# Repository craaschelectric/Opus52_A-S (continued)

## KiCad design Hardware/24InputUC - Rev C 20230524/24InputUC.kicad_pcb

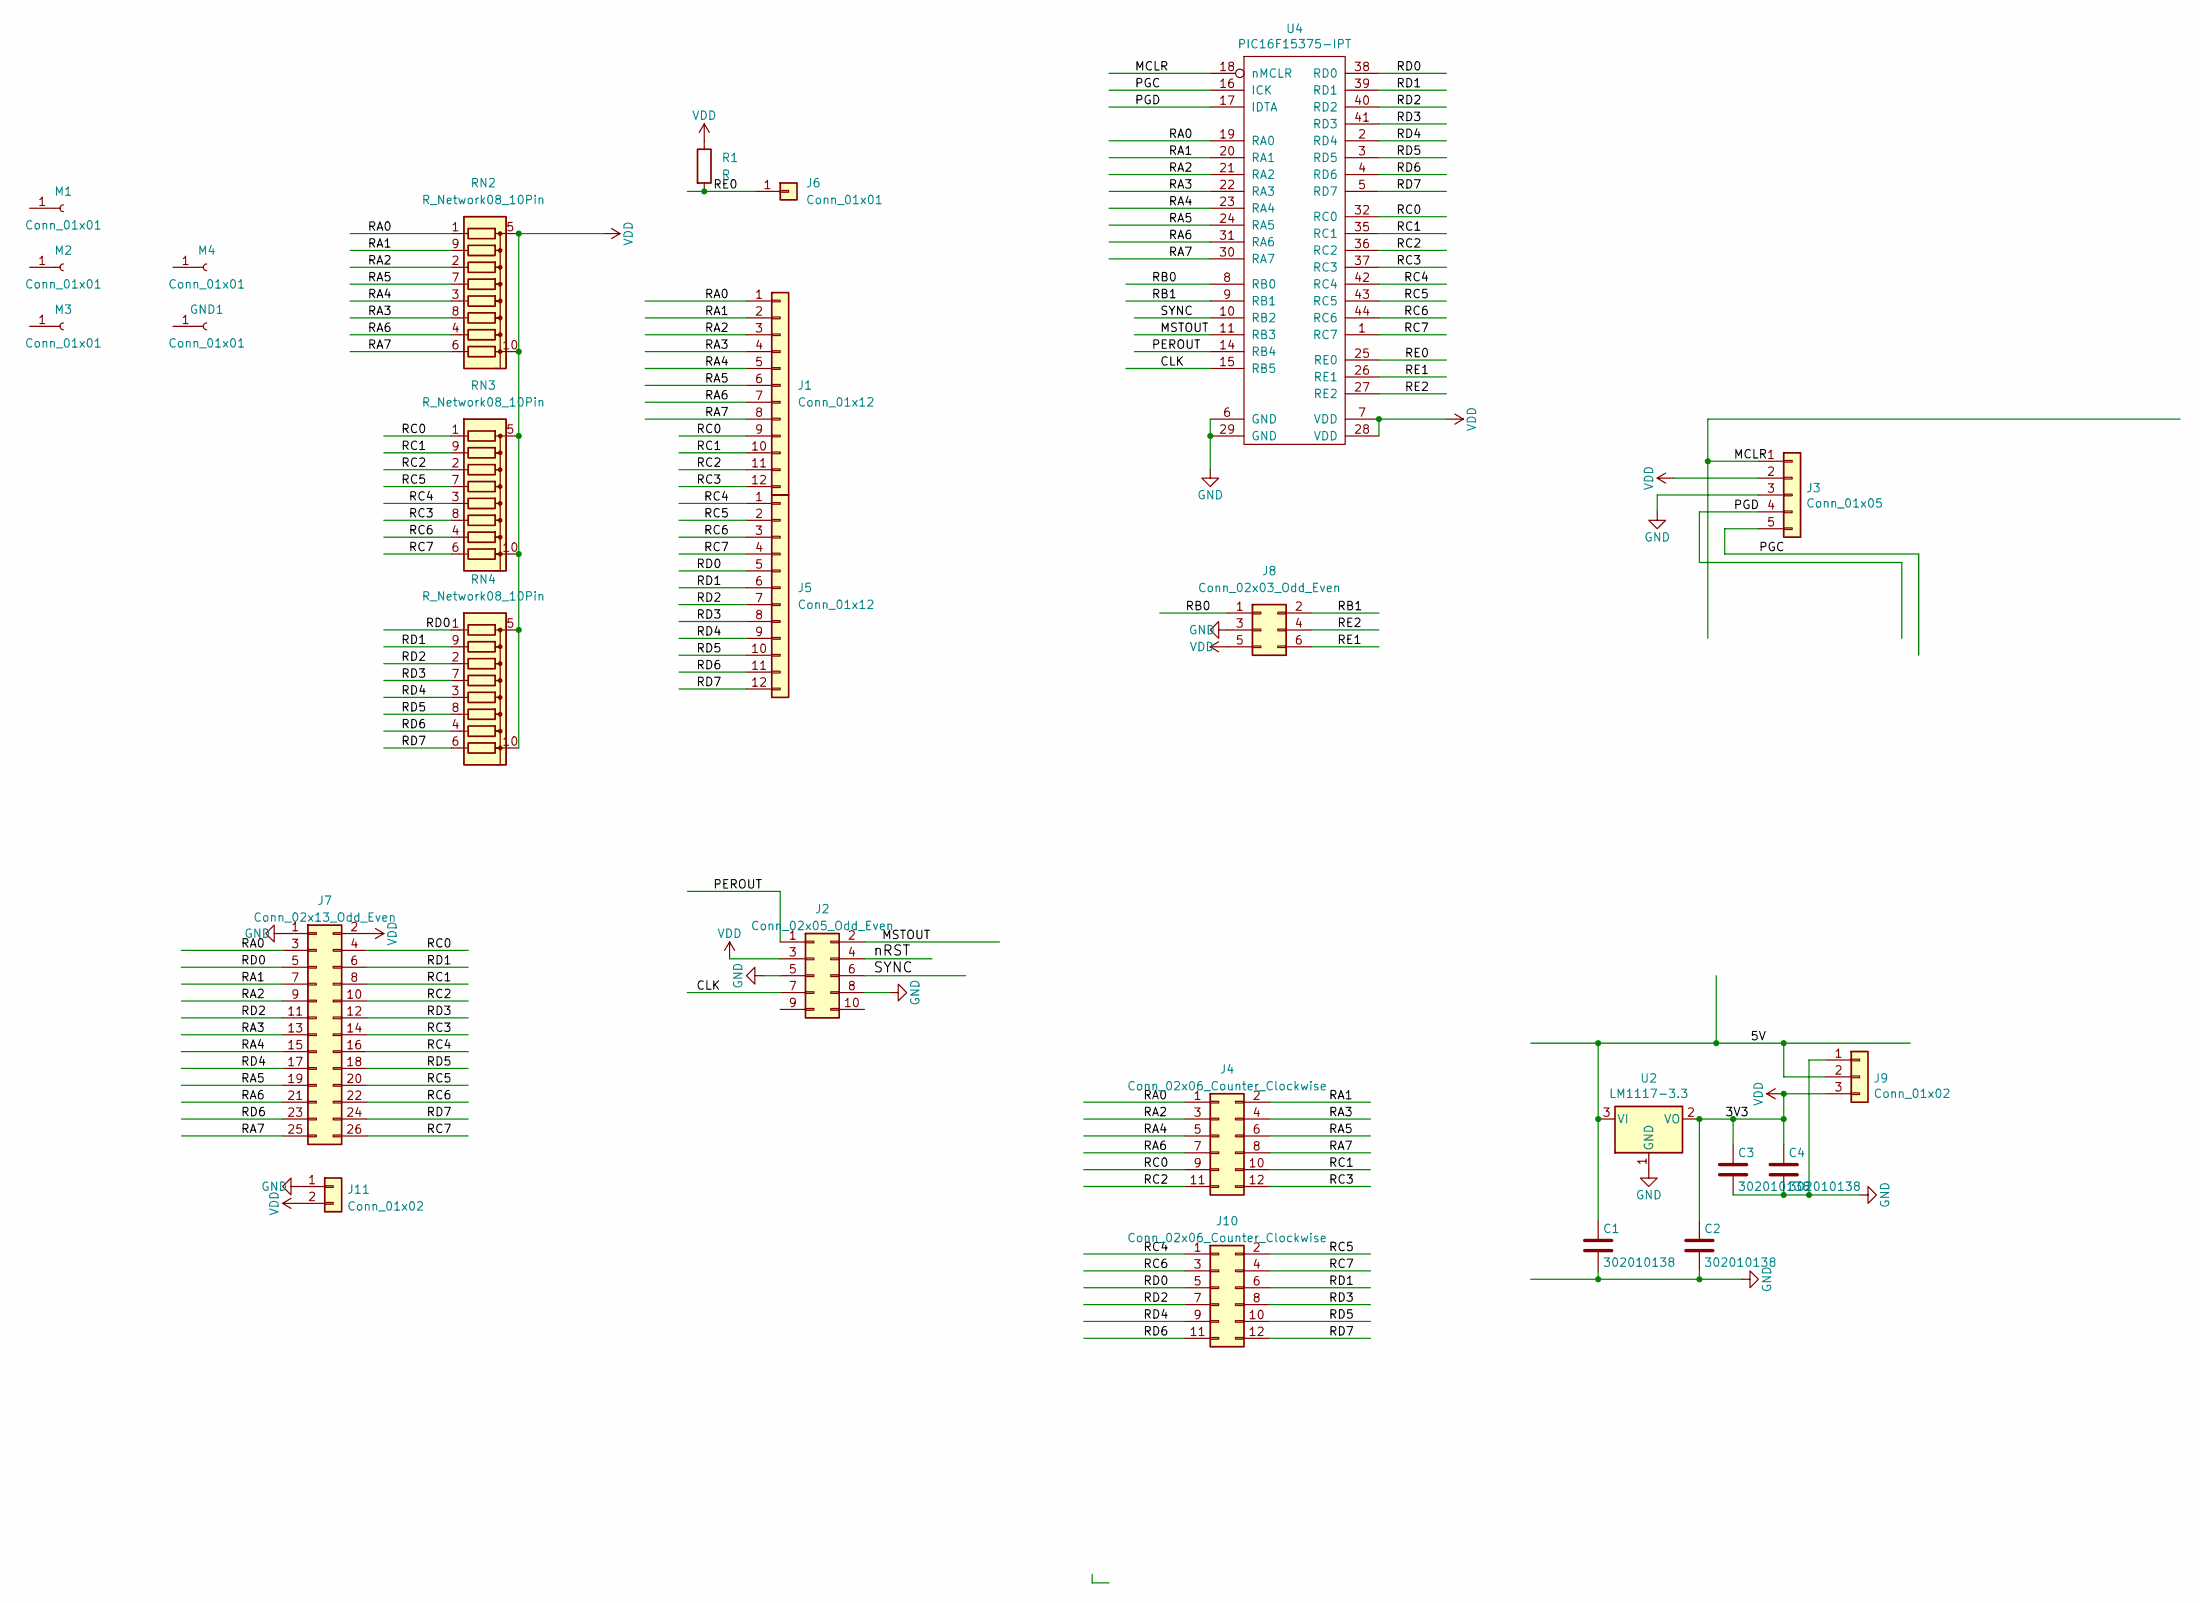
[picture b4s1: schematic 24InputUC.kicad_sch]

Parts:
C1, C3: 302010138; C_0805_2012Metric_Pad1.18x1.45mm_HandSolder
C2, C4: 302010138; C_0603_1608Metric_Pad1.08x0.95mm_HandSolder
GND1: Conn_01x01; KK156-1
J1, J5: Conn_01x12; KK156-12
J2: Conn_02x05_Odd_Even; RibbonCableSocket_10_OddEven
J3: Conn_01x05; PinHeader_1x06_P2.54mm_Vertical
J4, J10: Conn_02x06_Counter_Clockwise; RibbonCableSocket_12_OddEven
J6: Conn_01x01; KK156-1
J7: Conn_02x13_Odd_Even; RibbonCableSocket_26_OddEven
J8: Conn_02x03_Odd_Even; RibbonCableSocket_6_OddEven
J9: Conn_01x02; PinHeader_1x03_P2.54mm_Vertical
J11: Conn_01x02; PinHeader_1x02_P2.54mm_Vertical
M1, M2, M3, M4: Conn_01x01; Mounting#4
R1: R; R_0603_1608Metric_Pad0.98x0.95mm_HandSolder
RN2, RN3, RN4: R_Network08_10Pin; EXBA10P
U2: LM1117-3.3; SOT-223-3_TabPin2
U4: PIC16F15375-IPT; TQFP-44_10x10mm_P0.8mm

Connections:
/5V: C1.1, J9.2, U2.3 (VI)
/CLK: J2.7, U4.15 (RB5)
/MCLR: J3.1, U4.18 (nMCLR)
/MSTOUT: J2.2, U4.11 (RB3)
/PEROUT: J2.1, U4.14 (RB4)
/PGC: J3.5, U4.16 (ICK)
/PGD: J3.4, U4.17 (IDTA)
/RA0: J1.1, J4.1, J7.3, RN2.1 (common), U4.19 (RA0)
/RA1: J1.2, J4.2, J7.7, RN2.9 (R8), U4.20 (RA1)
/RA2: J1.3, J4.3, J7.9, RN2.2 (R1), U4.21 (RA2)
/RA3: J1.4, J4.4, J7.13, RN2.8 (R7), U4.22 (RA3)
/RA4: J1.5, J4.5, J7.15, RN2.3 (R2), U4.23 (RA4)
/RA5: J1.6, J4.6, J7.19, RN2.7 (R6), U4.24 (RA5)
/RA6: J1.7, J4.7, J7.21, RN2.4 (R3), U4.31 (RA6)
/RA7: J1.8, J4.8, J7.25, RN2.6 (R5), U4.30 (RA7)
/RB0: J8.1, U4.8 (RB0)
/RB1: J8.2, U4.9 (RB1)
/RC0: J1.9, J4.9, J7.4, RN3.1 (common), U4.32 (RC0)
/RC1: J1.10, J4.10, J7.8, RN3.9 (R8), U4.35 (RC1)
/RC2: J1.11, J4.11, J7.10, RN3.2 (R1), U4.36 (RC2)
/RC3: J1.12, J4.12, J7.14, RN3.8 (R7), U4.37 (RC3)
/RC4: J5.1, J7.16, J10.1, RN3.3 (R2), U4.42 (RC4)
/RC5: J5.2, J7.20, J10.2, RN3.7 (R6), U4.43 (RC5)
/RC6: J5.3, J7.22, J10.3, RN3.4 (R3), U4.44 (RC6)
/RC7: J5.4, J7.26, J10.4, RN3.6 (R5), U4.1 (RC7)
/RD0: J5.5, J7.5, J10.5, RN4.1 (common), U4.38 (RD0)
/RD1: J5.6, J7.6, J10.6, RN4.9 (R8), U4.39 (RD1)
/RD2: J5.7, J7.11, J10.7, RN4.2 (R1), U4.40 (RD2)
/RD3: J5.8, J7.12, J10.8, RN4.7 (R6), U4.41 (RD3)
/RD4: J5.9, J7.17, J10.9, RN4.3 (R2), U4.2 (RD4)
/RD5: J5.10, J7.18, J10.10, RN4.8 (R7), U4.3 (RD5)
/RD6: J5.11, J7.23, J10.11, RN4.4 (R3), U4.4 (RD6)
/RD7: J5.12, J7.24, J10.12, RN4.6 (R5), U4.5 (RD7)
/RE0: J6.1, R1.2, U4.25 (RE0)
/RE1: J8.6, U4.26 (RE1)
/RE2: J8.4, U4.27 (RE2)
/SYNC: J2.6, U4.10 (RB2)
/nRST: J2.4
GND: C1.2, C2.2, C3.2, C4.2, J2.5, J2.8, J3.3, J7.1, J8.3, J9.1, J11.1, U2.1 (GND), U4.6 (GND), U4.29 (GND)
VDD: C2.1, C3.1, C4.1, J2.3, J3.2, J7.2, J8.5, J9.3, J11.2, R1.1, RN2.5 (R4), RN2.10 (R9), RN3.5 (R4), RN3.10 (R9), RN4.5 (R4), RN4.10 (R9), U2.2 (VO), U4.7 (VDD), U4.28 (VDD)

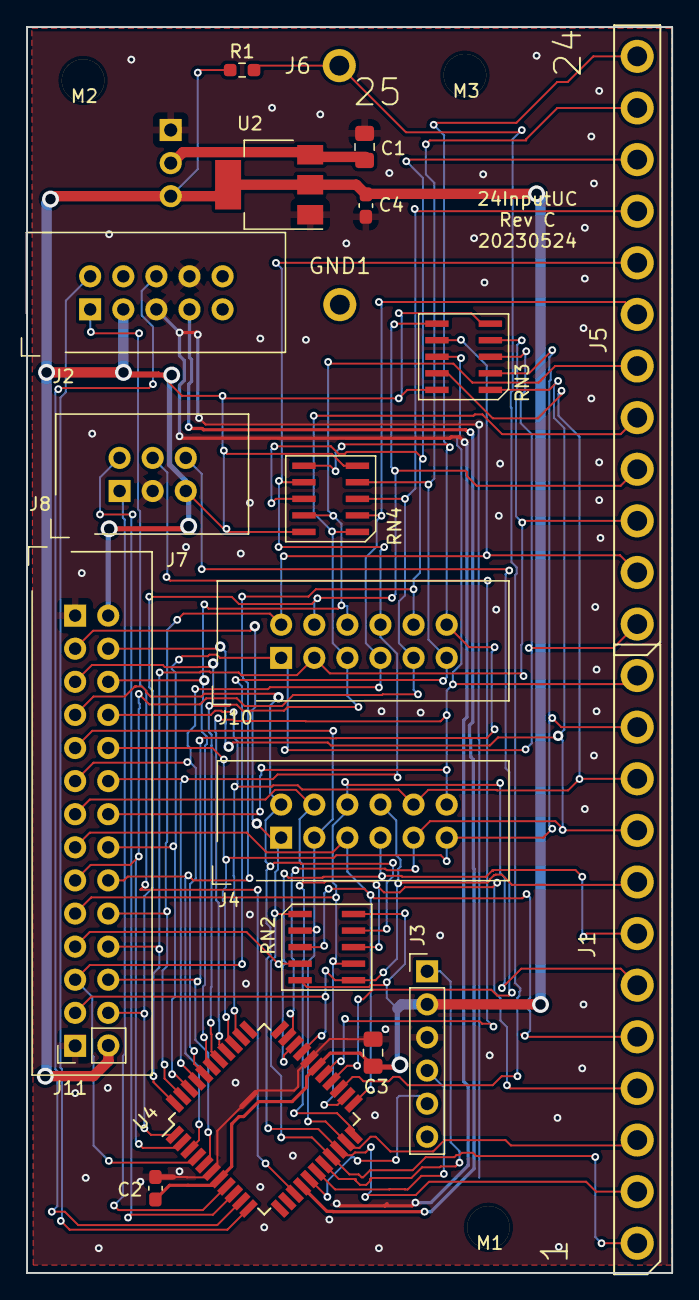
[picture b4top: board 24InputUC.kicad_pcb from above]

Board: 2 copper layers, 49.5 x 95.6 mm, 25 parts (1 on the bottom side), 39 nets.

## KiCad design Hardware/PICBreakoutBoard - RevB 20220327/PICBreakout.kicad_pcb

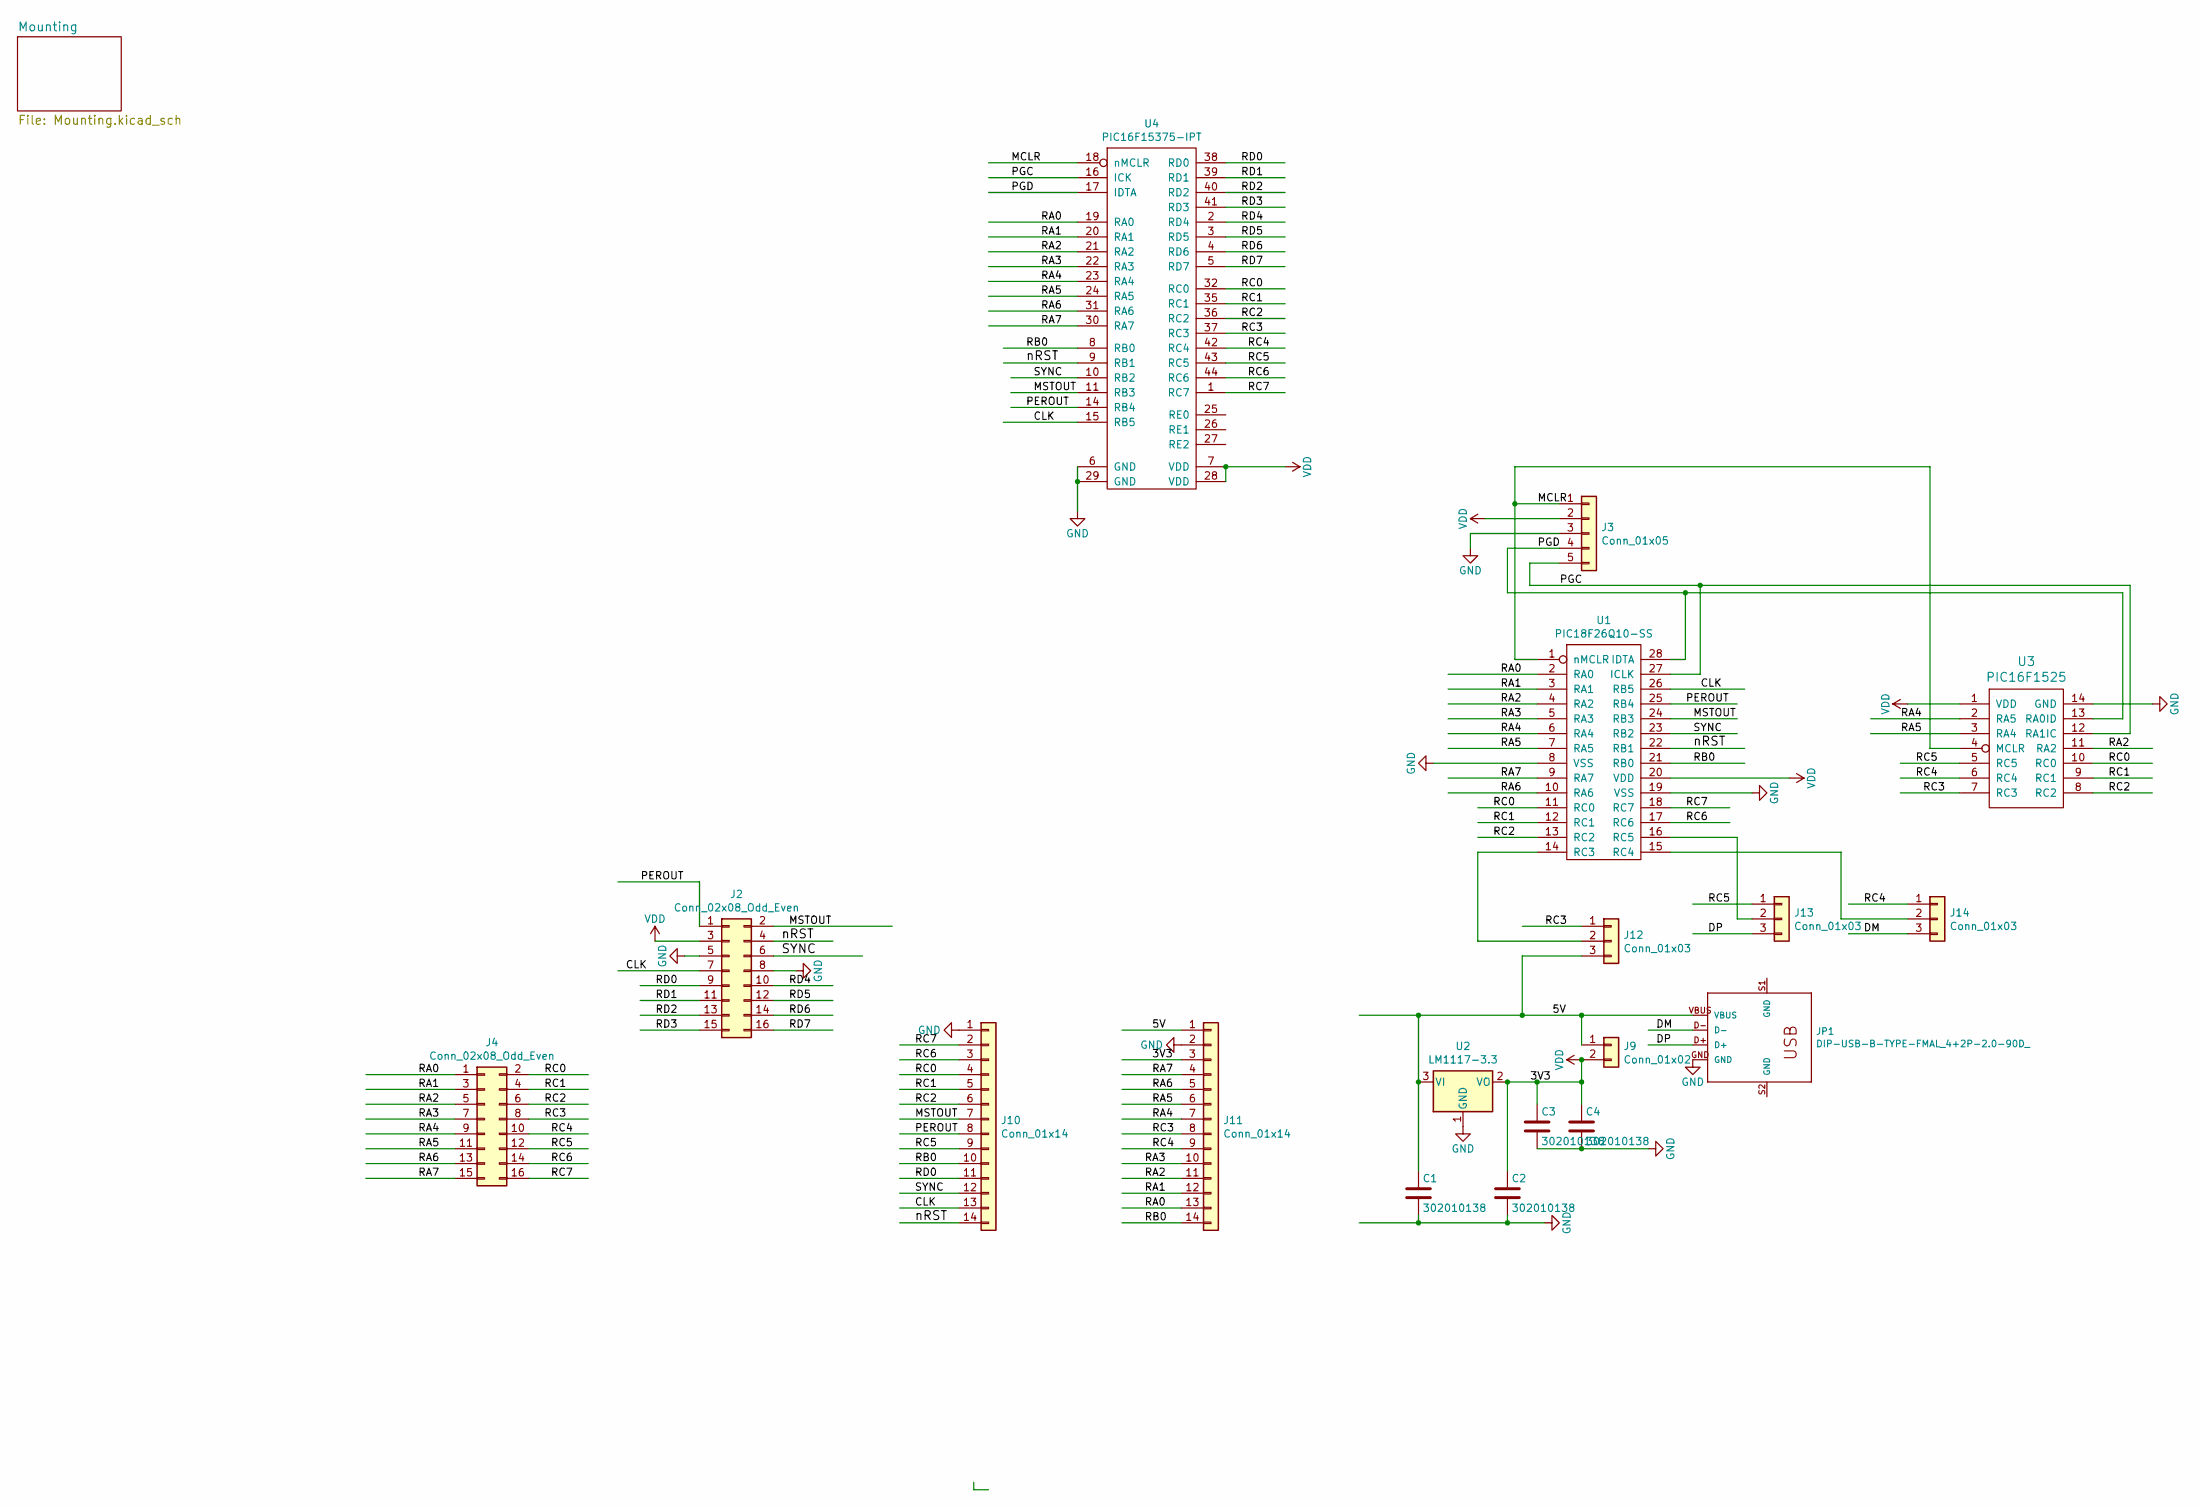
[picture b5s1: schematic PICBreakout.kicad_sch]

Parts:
C1, C3: 302010138; C_0805_2012Metric_Pad1.18x1.45mm_HandSolder
C2, C4: 302010138; C_0603_1608Metric_Pad1.08x0.95mm_HandSolder
J2, J4: Conn_02x08_Odd_Even; RibbonCableSocket_16_OddEven
J3: Conn_01x05; PinHeader_1x06_P2.54mm_Vertical
J9: Conn_01x02; H2-2.54
J10, J11: Conn_01x14; PinSocket_1x14_P2.54mm_Vertical
J12, J13, J14: Conn_01x03; 0603Jumper
JP1: DIP-USB-B-TYPE-FMAL_4+2P-2.0-90D_; USB4+2-2.5-90D-15.8X12MM
U1: PIC18F26Q10-SS; SSOP-28_5.3x10.2mm_P0.65mm
U2: LM1117-3.3; SOT-223-3_TabPin2
U3: PIC16F1525; SO-14_3.9x8.65mm_P1.27mm
U4: PIC16F15375-IPT; TQFP-44_10x10mm_P0.8mm

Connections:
/5V: C1.1, J9.1, J11.1, J12.3, JP1.VBUS, U2.3 (VI)
/CLK: J2.7, J10.13, U1.26 (RB5), U4.15 (RB5)
/DM: J14.3, JP1.D-
/DP: J13.3, JP1.D+
/MCLR: J3.1, U1.1 (nMCLR), U3.4 (MCLR), U4.18 (nMCLR)
/MSTOUT: J2.2, J10.7, U1.24 (RB3), U4.11 (RB3)
/PEROUT: J2.1, J10.8, U1.25 (RB4), U4.14 (RB4)
/PGC: J3.5, U1.27 (ICLK), U3.12 (RA1IC), U4.16 (ICK)
/PGD: J3.4, U1.28 (IDTA), U3.13 (RA0ID), U4.17 (IDTA)
/RA0: J4.1, J11.13, U1.2 (RA0), U4.19 (RA0)
/RA1: J4.3, J11.12, U1.3 (RA1), U4.20 (RA1)
/RA2: J4.5, J11.11, U1.4 (RA2), U3.11 (RA2), U4.21 (RA2)
/RA3: J4.7, J11.10, U1.5 (RA3), U4.22 (RA3)
/RA4: J4.9, J11.7, U1.6 (RA4), U3.2 (RA5), U4.23 (RA4)
/RA5: J4.11, J11.6, U1.7 (RA5), U3.3 (RA4), U4.24 (RA5)
/RA6: J4.13, J11.5, U1.10 (RA6), U4.31 (RA6)
/RA7: J4.15, J11.4, U1.9 (RA7), U4.30 (RA7)
/RB0: J10.10, J11.14, U1.21 (RB0), U4.8 (RB0)
/RC0: J4.2, J10.4, U1.11 (RC0), U3.10 (RC0), U4.32 (RC0)
/RC1: J4.4, J10.5, U1.12 (RC1), U3.9 (RC1), U4.35 (RC1)
/RC2: J4.6, J10.6, U1.13 (RC2), U3.8 (RC2), U4.36 (RC2)
/RC3: J4.8, J11.8, J12.1, U3.7 (RC3), U4.37 (RC3)
/RC4: J4.10, J11.9, J14.1, U3.6 (RC4), U4.42 (RC4)
/RC5: J4.12, J10.9, J13.1, U3.5 (RC5), U4.43 (RC5)
/RC6: J4.14, J10.3, U1.17 (RC6), U4.44 (RC6)
/RC7: J4.16, J10.2, U1.18 (RC7), U4.1 (RC7)
/RD0: J2.9, J10.11, U4.38 (RD0)
/RD1: J2.11, U4.39 (RD1)
/RD2: J2.13, U4.40 (RD2)
/RD3: J2.15, U4.41 (RD3)
/RD4: J2.10, U4.2 (RD4)
/RD5: J2.12, U4.3 (RD5)
/RD6: J2.14, U4.4 (RD6)
/RD7: J2.16, U4.5 (RD7)
/SYNC: J2.6, J10.12, U1.23 (RB2), U4.10 (RB2)
/nRST: J2.4, J10.14, U1.22 (RB1), U4.9 (RB1)
GND: C1.2, C2.2, C3.2, C4.2, J2.5, J2.8, J3.3, J10.1, J11.2, JP1.GND, U1.8 (VSS), U1.19 (VSS), U2.1 (GND), U3.14 (GND), U4.6 (GND), U4.29 (GND)
unnamed: J12.2, U1.14 (RC3)
unnamed: J13.2, U1.16 (RC5)
unnamed: J14.2, U1.15 (RC4)
VDD: C2.1, C3.1, C4.1, J2.3, J3.2, J9.2, J11.3, U1.20 (VDD), U2.2 (VO), U3.1 (VDD), U4.7 (VDD), U4.28 (VDD)

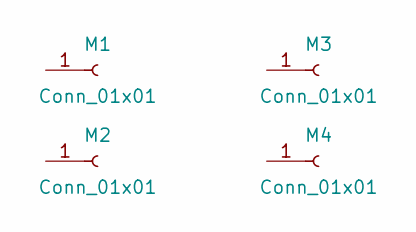
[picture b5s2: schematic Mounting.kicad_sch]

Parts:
M1, M2, M3, M4: Conn_01x01; Mounting#4

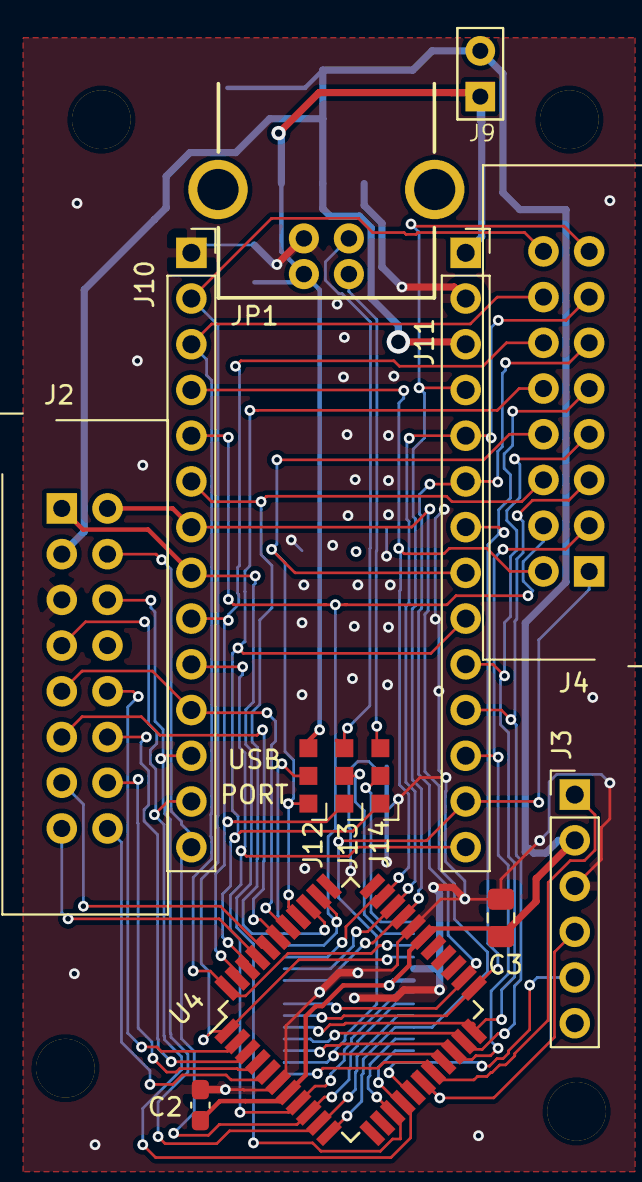
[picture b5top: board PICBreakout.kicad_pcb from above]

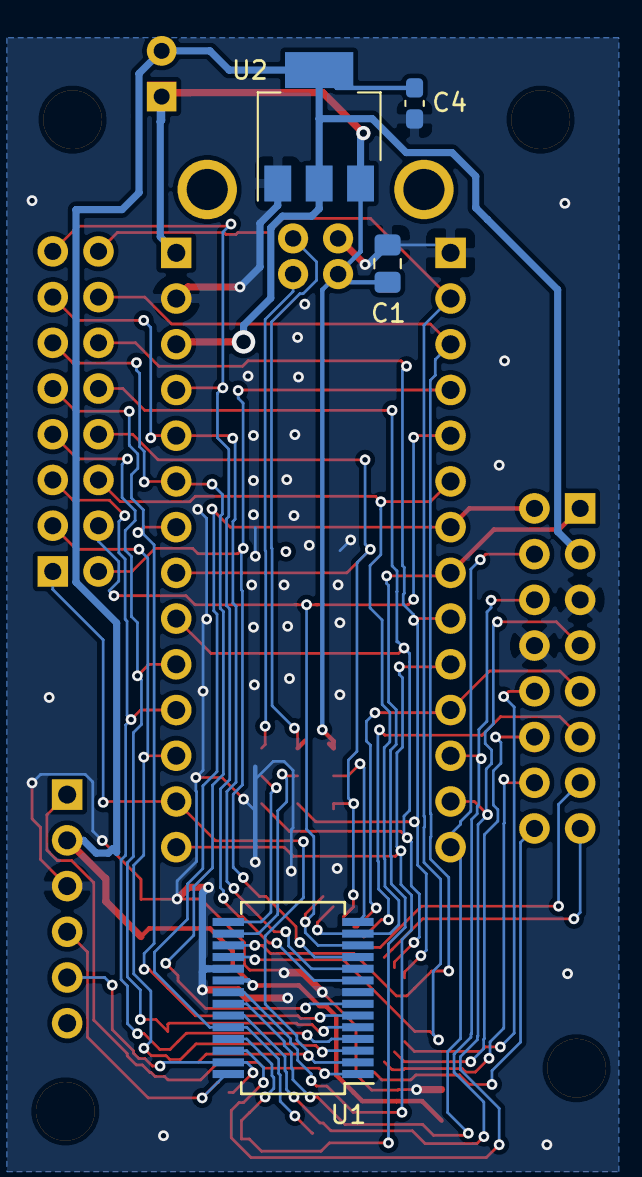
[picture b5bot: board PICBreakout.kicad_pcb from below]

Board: 2 copper layers, 21 parts (4 on the bottom side), 41 nets.

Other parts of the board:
Me: Conn_01x01; Mounting#4

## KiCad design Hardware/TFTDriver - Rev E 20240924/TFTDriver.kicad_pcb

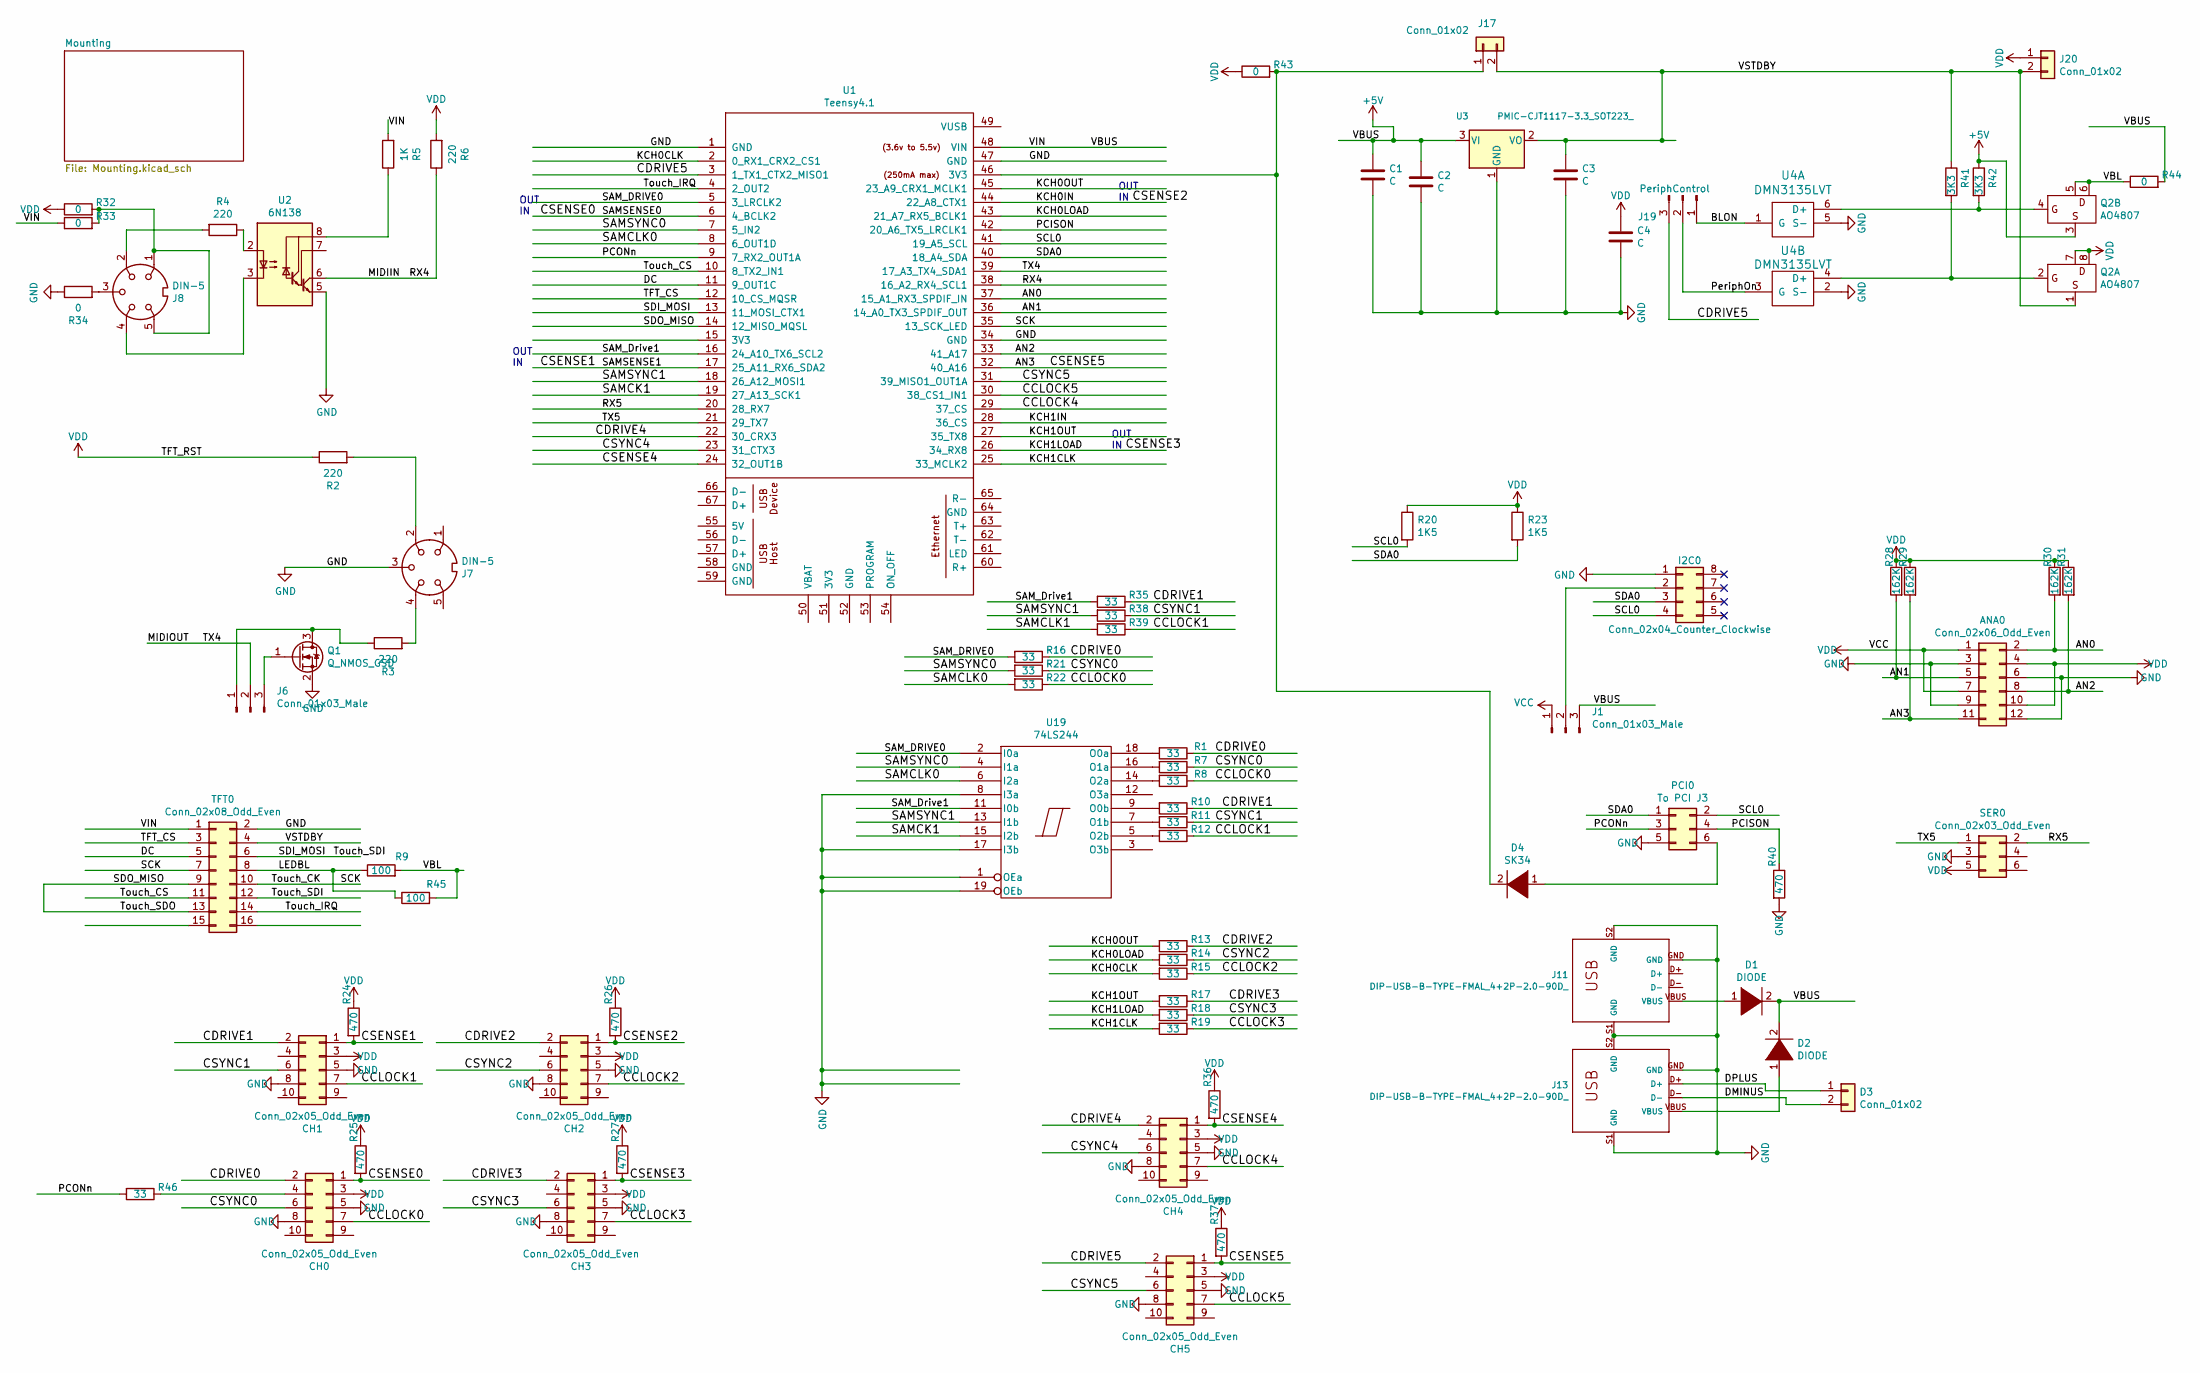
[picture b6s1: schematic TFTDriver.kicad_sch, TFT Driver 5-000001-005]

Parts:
ANA0: Conn_02x06_Odd_Even; RibbonCableSocket_12_OddEven
C1, C4: C; C_0603_1608Metric_Pad1.08x0.95mm_HandSolder
C2, C3: C; C_0805_2012Metric_Pad1.18x1.45mm_HandSolder
CH0, CH1, CH2, CH3, CH4, CH5: Conn_02x05_Odd_Even; RibbonCableSocket_10_OddEven
D1, D2: DIODE; D_SMA_Handsoldering_APin1
D3: Conn_01x02; PinHeader_1x02_P2.54mm_Vertical
D4: SK34; D_SMA_Handsoldering
I2C0: Conn_02x04_Counter_Clockwise; RibbonCableSocket_8_CCW
J1: Conn_01x03_Male; PinHeader_1x03_P2.54mm_Vertical
J6: Conn_01x03_Male; H3-2.54
J7, J8: DIN-5; DIN5_KCDX-5S-S2
J11, J13: DIP-USB-B-TYPE-FMAL_4+2P-2.0-90D_; USB4+2-2.5-90D-15.8X12MM
J17, J20: Conn_01x02; PinHeader_1x02_P2.54mm_Vertical
J19: PeriphControl; 0603Jumper
PCI0: To PCI J3; RibbonCableSocket_6_OddEven
Q1: Q_NMOS_GSD; SOT-23_Handsoldering
Q2: AO4807; SOIC-8_3.9x4.9mm_P1.27mm
R1, R7, R8, R10, R11, R12, R13, R14, R15, R16, R17, R18, R19, R21, R22, R35, R38, R39, R46: 33; R_0603_1608Metric_Pad0.98x0.95mm_HandSolder
R2, R3, R4, R6: 220; R_0603_1608Metric_Pad0.98x0.95mm_HandSolder
R5: 1K; R_0603_1608Metric_Pad0.98x0.95mm_HandSolder
R9: 100; PinHeader_1x02_P2.54mm_Vertical
R20, R23: 1K5; R_0603_1608Metric_Pad0.98x0.95mm_HandSolder
R24, R25, R26, R27, R36, R37, R40: 470; R_0603_1608Metric_Pad0.98x0.95mm_HandSolder
R28, R29, R30, R31: 162K; R_0603_1608Metric_Pad0.98x0.95mm_HandSolder
R32, R33, R34, R43, R44: 0; R_0603_1608Metric_Pad0.98x0.95mm_HandSolder
R41, R42: 3K3; R_0603_1608Metric_Pad0.98x0.95mm_HandSolder
R45: 100; R_1206_3216Metric_Pad1.30x1.75mm_HandSolder
SER0: Conn_02x03_Odd_Even; RibbonCableSocket_6_OddEven
TFT0: Conn_02x08_Odd_Even; RibbonCableSocket_16_OddEven
U1: Teensy4.1; Teensy41
U2: 6N138; DIP-8_W7.62mm
U3: PMIC-CJT1117-3.3_SOT223_; SOT-223; MPN CJT1117-3.3
U4: DMN3135LVT; SOT-23-6_Handsoldering
U19: 74LS244; SSOP-20_4.4x6.5mm_P0.65mm

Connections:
+5V: C1.1, C2.1, D1.2 (A), D2.2 (A), J1.3, Q2.3, R5.2, R33.1, R42.1, R44.2, TFT0.1, U1.48 (VIN), U3.3 (VI)
/AN0: ANA0.2, R30.2, U1.37 (15_A1_RX3_SPDIF_IN)
/AN1: ANA0.5, R28.2, U1.36 (14_A0_TX3_SPDIF_OUT)
/AN2: ANA0.8, R31.2, U1.33 (41_A17)
/AN3: ANA0.11, CH5.1, R29.2, R37.2, U1.32 (40_A16)
/BLON: J19.1, U4.1 (G)
/CCLOCK0: CH0.7, R8.1, R22.1
/CCLOCK1: CH1.7, R12.1, R39.1
/CCLOCK2: CH2.7, R15.1
/CCLOCK3: CH3.7, R19.1
/CCLOCK4: CH4.7, U1.29 (37_CS)
/CCLOCK5: CH5.7, U1.30 (38_CS1_IN1)
/CDRIVE0: CH0.2, R1.1, R16.1
/CDRIVE1: CH1.2, R10.1, R35.1
/CDRIVE2: CH2.2, R13.1
/CDRIVE3: CH3.2, R17.1
/CDRIVE4: CH4.2, U1.22 (30_CRX3)
/CDRIVE5: CH5.2, J19.3, U1.3 (1_TX1_CTX2_MISO1)
/CSENSE0: CH0.1, R25.2, U1.6 (4_BCLK2)
/CSENSE1: CH1.1, R24.2, U1.17 (25_A11_RX6_SDA2)
/CSENSE2: CH2.1, R26.2, U1.44 (22_A8_CTX1)
/CSENSE3: CH3.1, R18.2, R27.2, U1.26 (34_RX8)
/CSENSE4: CH4.1, R36.2, U1.24 (32_OUT1B)
/CSYNC0: CH0.6, R7.1, R21.1
/CSYNC1: CH1.6, R11.1, R38.1
/CSYNC2: CH2.6, R14.1
/CSYNC3: CH3.6, R18.1
/CSYNC4: CH4.6, U1.23 (31_CTX3)
/CSYNC5: CH5.6, U1.31 (39_MISO1_OUT1A)
/DC: TFT0.5, U1.11 (9_OUT1C)
/DMINUS: D3.2, J13.D-
/DPLUS: D3.1, J13.D+
/KCH0CLK: R15.2, U1.2 (0_RX1_CRX2_CS1)
/KCH0LOAD: R14.2, U1.43 (21_A7_RX5_BCLK1)
/KCH0OUT: R13.2, U1.45 (23_A9_CRX1_MCLK1)
/KCH1CLK: R19.2, U1.25 (33_MCLK2)
/KCH1IN: U1.28 (36_CS)
/KCH1OUT: R17.2, U1.27 (35_TX8)
/LEDBL: R9.1, R45.1, TFT0.8
/MIDIIN: R6.1, U1.38 (16_A2_RX4_SCL1), U2.6 (VO2)
/MIDIOUT: J6.2, U1.39 (17_A3_TX4_SDA1)
/PCISON: PCI0.4, R40.1, U1.42 (20_A6_TX5_LRCLK1)
/PCONn: PCI0.3, R46.2, U1.9 (7_RX2_OUT1A)
/PeriphOn: J19.2, U4.3 (G)
/RX5: SER0.2, U1.20 (28_RX7)
/SAMCK1: U1.19 (27_A13_SCK1), U19.15 (I2b)
/SAMCLK0: R22.2, U1.8 (6_OUT1D), U19.6 (I2a)
/SAMCLK1: R39.2
/SAMSYNC0: R21.2, U1.7 (5_IN2), U19.4 (I1a)
/SAMSYNC1: R38.2, U1.18 (26_A12_MOSI1), U19.13 (I1b)
/SAM_DRIVE0: R16.2, U1.5 (3_LRCLK2), U19.2 (I0a)
/SAM_Drive1: R35.2, U1.16 (24_A10_TX6_SCL2), U19.11 (I0b)
/SCK: TFT0.7, TFT0.10, U1.35 (13_SCK_LED)
/SCL0: I2C0.4, PCI0.2, R20.2, U1.41 (19_A5_SCL)
/SDA0: I2C0.3, PCI0.1, R23.2, U1.40 (18_A4_SDA)
/SDI_MOSI: TFT0.6, TFT0.12, U1.13 (11_MOSI_CTX1)
/SDO_MISO: TFT0.9, TFT0.13, U1.14 (12_MISO_MQSL)
/TFT_CS: TFT0.3, U1.12 (10_CS_MQSR)
/TX5: SER0.1, U1.21 (29_TX7)
/Touch_CS: TFT0.11, U1.10 (8_TX2_IN1)
/Touch_IRQ: TFT0.14, U1.4 (2_OUT2)
/VBL: Q2.5, Q2.6, R9.2, R44.1, R45.2
/VSTDBY: C3.1, J17.2, J20.2, Q2.1, R41.1, TFT0.4, U3.2 (VO), U3.4
GND: ANA0.3, ANA0.6, ANA0.9, ANA0.12, C1.2, C2.2, C3.2, C4.2, CH0.5, CH0.8, CH1.5, CH1.8, CH2.5, CH2.8, CH3.5, CH3.8, CH4.5, CH4.8, CH5.5, CH5.8, I2C0.1, J7.3, J11.GND, J11.S1 (GND), J11.S2 (GND), J13.GND, J13.S1 (GND), J13.S2 (GND), PCI0.5, Q1.2 (S), R34.1, R40.2, SER0.3, TFT0.2, U1.1 (GND), U1.34 (GND), U1.47 (GND), U2.5 (GND), U3.1 (GND), U4.2 (S-), U4.5 (S-), U19.1 (OEa), U19.8 (I3a), U19.10 (GND), U19.17 (I3b), U19.19 (OEb)
unnamed: CH0.4, R46.1
unnamed: D1.1 (K), J11.VBUS
unnamed: D2.1 (K), J13.VBUS
unnamed: D4.2 (A), J17.1, R43.2, U1.46 (3V3)
unnamed: D4.1 (K), PCI0.6
unnamed: I2C0.2, J1.2
unnamed: J6.1, Q1.3 (D), R3.1
unnamed: J6.3, Q1.1 (G)
unnamed: J7.2, R2.2
unnamed: J7.4, R3.2
unnamed: J8.1, J8.5, R32.2, R33.2
unnamed: J8.2, R4.2
unnamed: J8.3, R34.2
unnamed: R4.1, U2.2 (C1)
unnamed: J8.4, U2.3 (C2)
unnamed: R5.1, U2.8 (VCC)
unnamed: Q2.4, R42.2, U4.6 (D+)
unnamed: Q2.2, R41.2, U4.4 (D+)
unnamed: R1.2, U19.18 (O0a)
unnamed: R10.2, U19.9 (O0b)
unnamed: R7.2, U19.16 (O1a)
unnamed: R11.2, U19.7 (O1b)
unnamed: R8.2, U19.14 (O2a)
unnamed: R12.2, U19.5 (O2b)
VCC: ANA0.1, ANA0.4, ANA0.7, ANA0.10, C4.1, CH0.3, CH1.3, CH2.3, CH3.3, CH4.3, CH5.3, J1.1, J20.1, Q2.7, Q2.8, R2.1, R6.2, R20.1, R23.1, R24.1, R25.1, R26.1, R27.1, R28.1, R29.1, R30.1, R31.1, R32.1, R36.1, R37.1, R43.1, SER0.5, U19.20 (VCC)

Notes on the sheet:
OUT IN

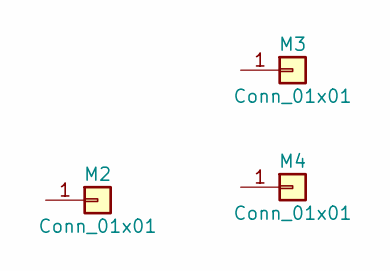
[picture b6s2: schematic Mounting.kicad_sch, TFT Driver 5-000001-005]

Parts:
M2, M3, M4: Conn_01x01; Mounting#4

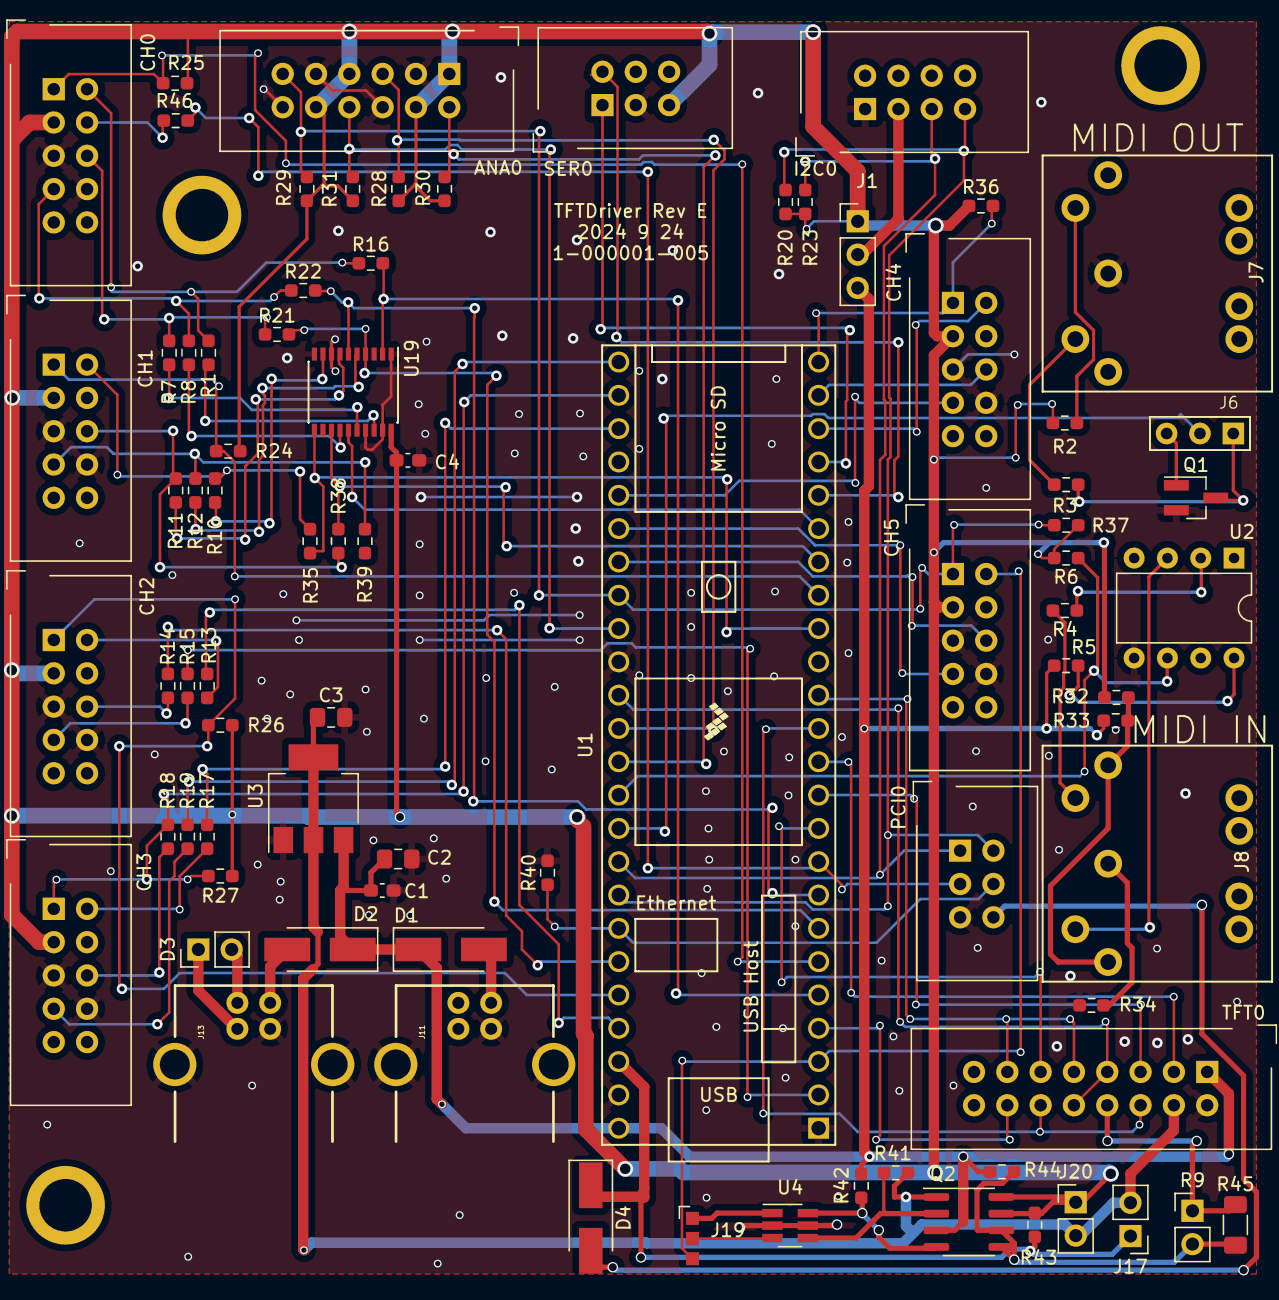
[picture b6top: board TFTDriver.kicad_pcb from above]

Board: 2 copper layers, 84 parts (0 on the bottom side), 87 nets.
